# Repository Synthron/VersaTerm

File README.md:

# VersaTerm

Adaptation of https://github.com/dhansel/VersaTerm/tree/main

## Changes

- Integrated Pi Pico and MAX3232
- Additional USB A Port for Power to Display
- Integrated 3V3 SMPS
- No 12V connector, Power Supply via USB or UART (5V TTL only)

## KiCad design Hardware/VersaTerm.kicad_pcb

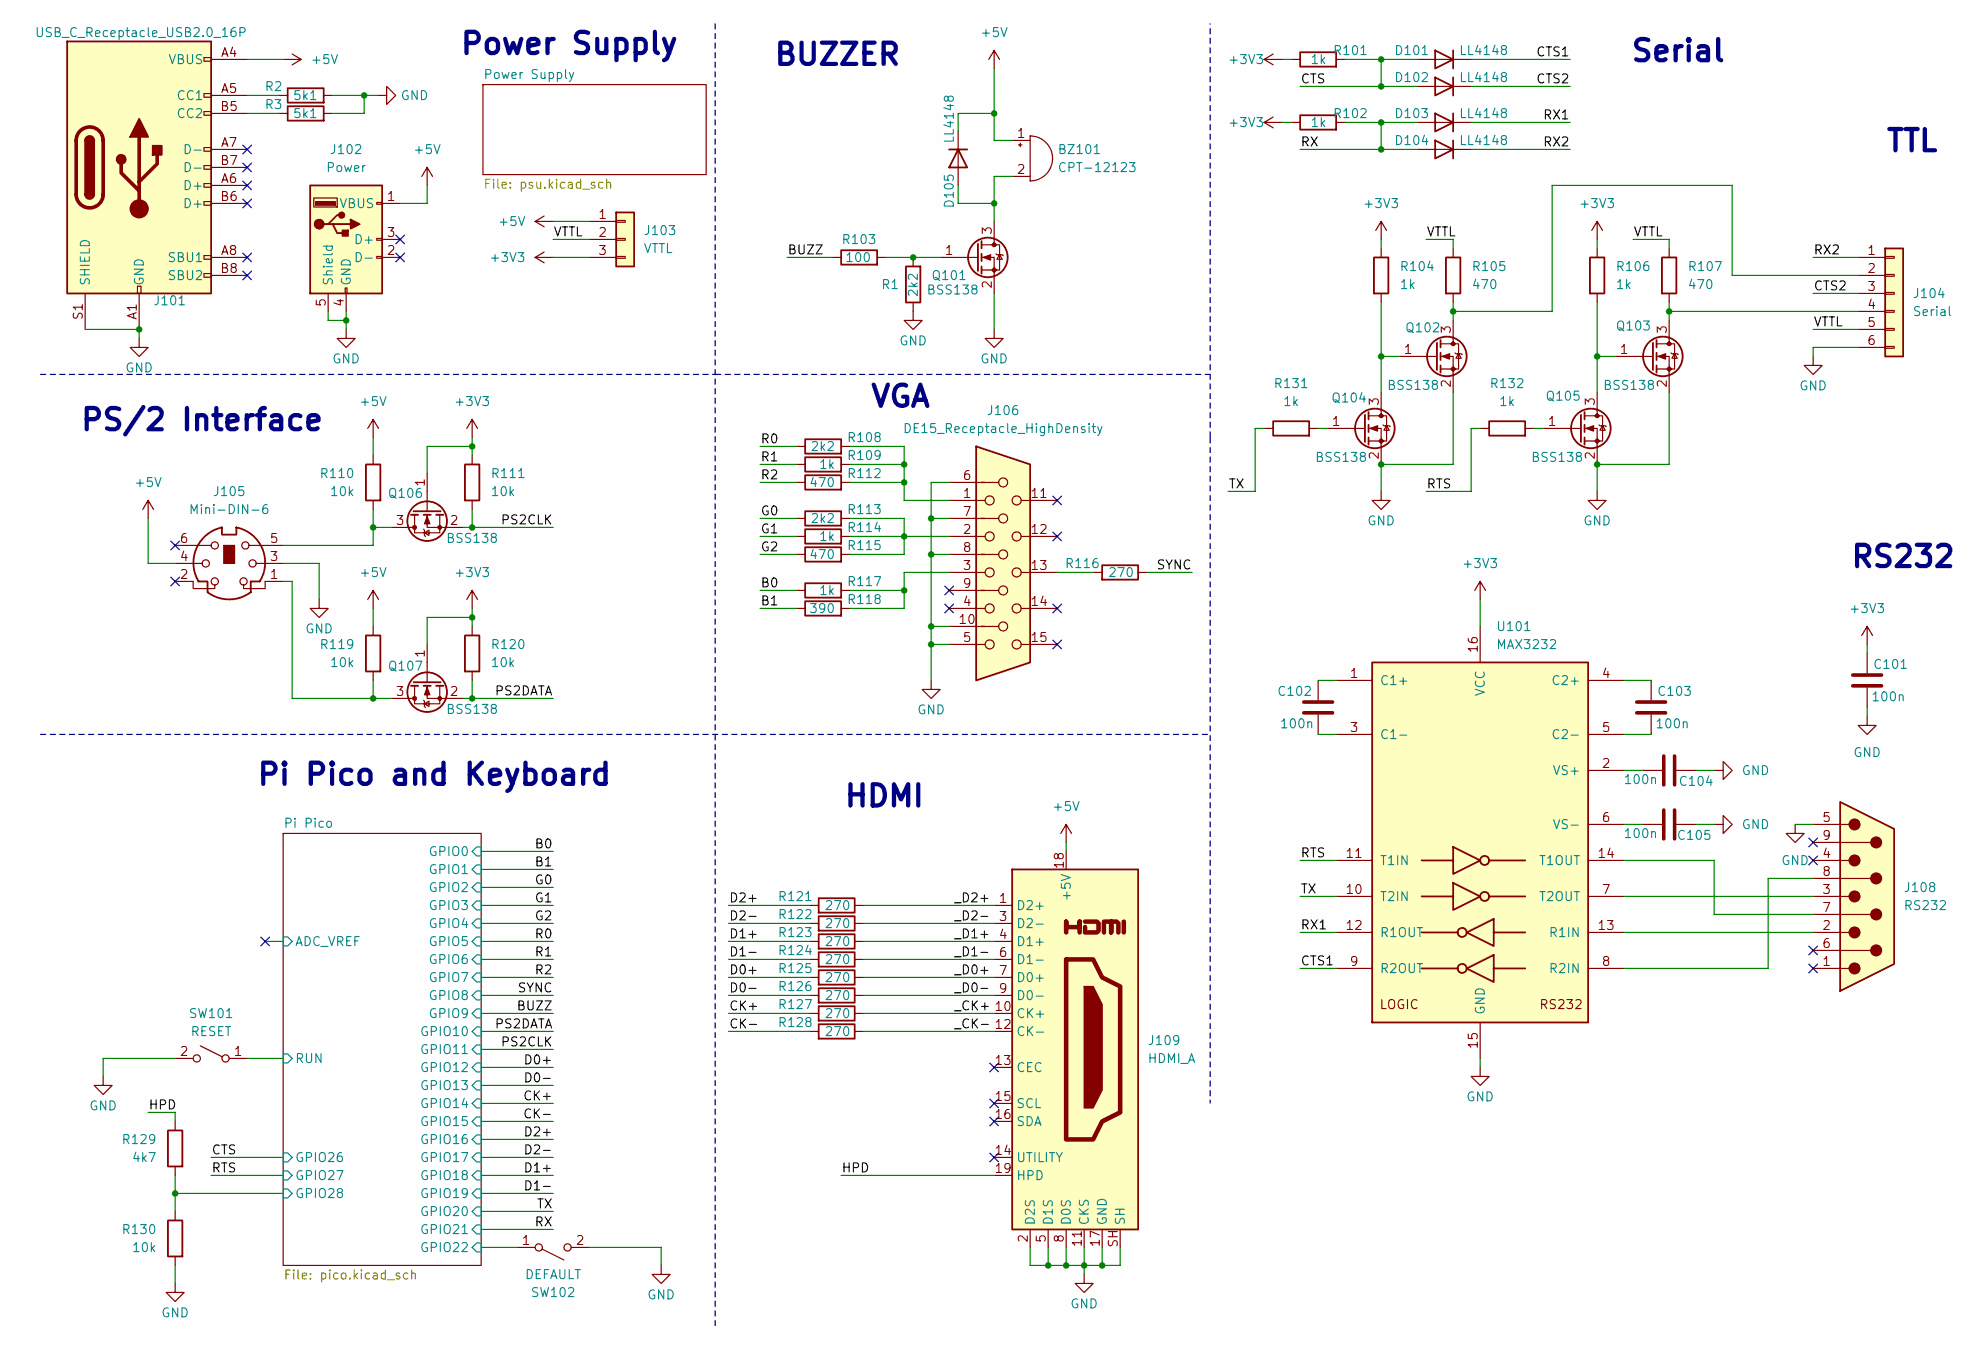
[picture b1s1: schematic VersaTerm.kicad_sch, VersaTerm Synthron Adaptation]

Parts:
BZ101: CPT-12123; Buzzer_Mallory_AST1240MLQ
C101, C102, C103, C104, C105: 100n; C_0805_2012Metric
D101, D102, D103, D104, D105: LL4148; D_MiniMELF
J101: USB_C_Receptacle_USB2.0_16P; USB_C_Receptacle_G-Switch_GT-USB-7010ASV
J102: Power; USB_A_CONNFLY_DS1095-WNR0
J103: VTTL; PinHeader_1x03_P2.54mm_Horizontal
J104: Serial; PinHeader_1x06_P2.54mm_Horizontal
J105: Mini-DIN-6; 57500711
J106: DE15_Receptacle_HighDensity; DSUB-15-HD_Female_Horizontal_P2.29x1.98mm_EdgePinOffset8.35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
J108: RS232; DSUB-9_Male_Horizontal_P2.77x2.84mm_EdgePinOffset7.70mm_Hou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
J109: HDMI_A; AMPHENOL_10029449-111RLF
Q101, Q102, Q103, Q104, Q105, Q106, Q107: BSS138; SOT-23
R1, R108, R113: 2k2; R_0805_2012Metric
R2, R3: 5k1; R_0805_2012Metric
R101, R102, R104, R106, R109, R114, R117, R131, R132: 1k; R_0805_2012Metric
R103: 100; R_0805_2012Metric
R105, R107, R112, R115: 470; R_0805_2012Metric
R110, R111, R119, R120, R130: 10k; R_0805_2012Metric
R116, R121, R122, R123, R124, R125, R126, R127, R128: 270; R_0805_2012Metric
R118: 390; R_0805_2012Metric
R129: 4k7; R_0805_2012Metric
SW101: RESET; SW_SPST_Omron_B3F-315x_Angled
SW102: DEFAULT; SW_SPST_Omron_B3F-315x_Angled
U101: MAX3232; TSSOP-16_4.4x5mm_P0.65mm

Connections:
+3V3: C101.1, J103.3, Q106.1 (G), Q107.1 (G), R101.1, R102.1, R104.1, R106.1, R111.1, R120.1, U101.16 (VCC); also elsewhere on the board
+5V: BZ101.1 (+), D105.1 (K), J101.A4 (VBUS), J101.A9 (VBUS), J101.B4 (VBUS), J101.B9 (VBUS), J102.1 (VBUS), J103.1, J105.4, J109.18 (+5V), R110.1, R119.1; also elsewhere on the board
/B0: R117.1; also elsewhere on the board
/B1: R118.1; also elsewhere on the board
/BUZZ: R103.1; also elsewhere on the board
/CK+: R127.2; also elsewhere on the board
/CK-: R128.2; also elsewhere on the board
/CTS: D101.2 (A), D102.2 (A), R101.2; also elsewhere on the board
/CTS1: D101.1 (K), U101.9 (R2OUT)
/CTS2: D102.1 (K), J104.3
/D0+: R125.2; also elsewhere on the board
/D0-: R126.2; also elsewhere on the board
/D1+: R123.2; also elsewhere on the board
/D1-: R124.2; also elsewhere on the board
/D2+: R121.2; also elsewhere on the board
/D2-: R122.2; also elsewhere on the board
/G0: R113.1; also elsewhere on the board
/G1: R114.1; also elsewhere on the board
/G2: R115.1; also elsewhere on the board
/HPD: J109.19 (HPD), R129.1
/PS2CLK: Q106.2 (S), R111.2; also elsewhere on the board
/PS2DATA: Q107.2 (S), R120.2; also elsewhere on the board
/Pi Pico/ADC2: R129.2, R130.1; also elsewhere on the board
/Pi Pico/GPIO22: SW102.1 (A); also elsewhere on the board
/Pi Pico/RUN: SW101.1 (A); also elsewhere on the board
/R0: R108.1; also elsewhere on the board
/R1: R109.1; also elsewhere on the board
/R2: R112.1; also elsewhere on the board
/RTS: R132.1, U101.11 (T1IN); also elsewhere on the board
/RX: D103.2 (A), D104.2 (A), R102.2; also elsewhere on the board
/RX1: D103.1 (K), U101.12 (R1OUT)
/RX2: D104.1 (K), J104.1
/SYNC: R116.1; also elsewhere on the board
/TX: R131.1, U101.10 (T2IN); also elsewhere on the board
/VTTL: J103.2, J104.5, R105.1, R107.1
/_CK+: J109.10 (CK+), R127.1
/_CK-: J109.12 (CK-), R128.1
/_D0+: J109.7 (D0+), R125.1
/_D0-: J109.9 (D0-), R126.1
/_D1+: J109.4 (D1+), R123.1
/_D1-: J109.6 (D1-), R124.1
/_D2+: J109.1 (D2+), R121.1
/_D2-: J109.3 (D2-), R122.1
GND: C101.2, C104.2, C105.2, J101.A1 (GND), J101.A12 (GND), J101.B1 (GND), J101.B12 (GND), J101.S1 (SHIELD), J102.4 (GND), J102.5 (Shield), J104.6, J105.3, J106.5, J106.6, J106.7, J106.8, J106.10, J108.5, J109.2 (D2S), J109.5 (D1S), J109.8 (D0S), J109.11 (CKS), J109.17 (GND), J109.SH, Q101.2 (S), Q102.2 (S), Q103.2 (S), Q104.2 (S), Q105.2 (S), R1.1, R2.2, R3.2, R130.2, SW101.2 (B), SW102.2 (B), U101.15 (GND); also elsewhere on the board
unnamed: BZ101.2 (-), D105.2 (A), Q101.3 (D)
unnamed: J101.A5 (CC1), R2.1
unnamed: J101.B5 (CC2), R3.1
unnamed: J104.2, Q102.3 (D), R105.2
unnamed: J104.4, Q103.3 (D), R107.2
unnamed: J106.1, R108.2, R109.2, R112.2
unnamed: J106.2, R113.2, R114.2, R115.2
unnamed: J106.3, R117.2, R118.2
unnamed: J106.13, R116.2
unnamed: Q101.1 (G), R1.2, R103.2
unnamed: Q102.1 (G), Q104.3 (D), R104.2
unnamed: Q103.1 (G), Q105.3 (D), R106.2
unnamed: Q104.1 (G), R131.2
unnamed: Q105.1 (G), R132.2
unnamed: J105.5, Q106.3 (D), R110.2
unnamed: J105.1, Q107.3 (D), R119.2
unnamed: C102.1, U101.1 (C1+)
unnamed: C102.2, U101.3 (C1-)
unnamed: C103.1, U101.4 (C2+)
unnamed: C103.2, U101.5 (C2-)
unnamed: J108.2, U101.13 (R1IN)
unnamed: J108.8, U101.8 (R2IN)
unnamed: J108.7, U101.14 (T1OUT)
unnamed: J108.3, U101.7 (T2OUT)
unnamed: C104.1, U101.2 (VS+)
unnamed: C105.1, U101.6 (VS-)

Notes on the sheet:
Pi Pico and Keyboard
Serial
HDMI
BUZZER
VGA
TTL
PS/2 Interface
Power Supply
RS232

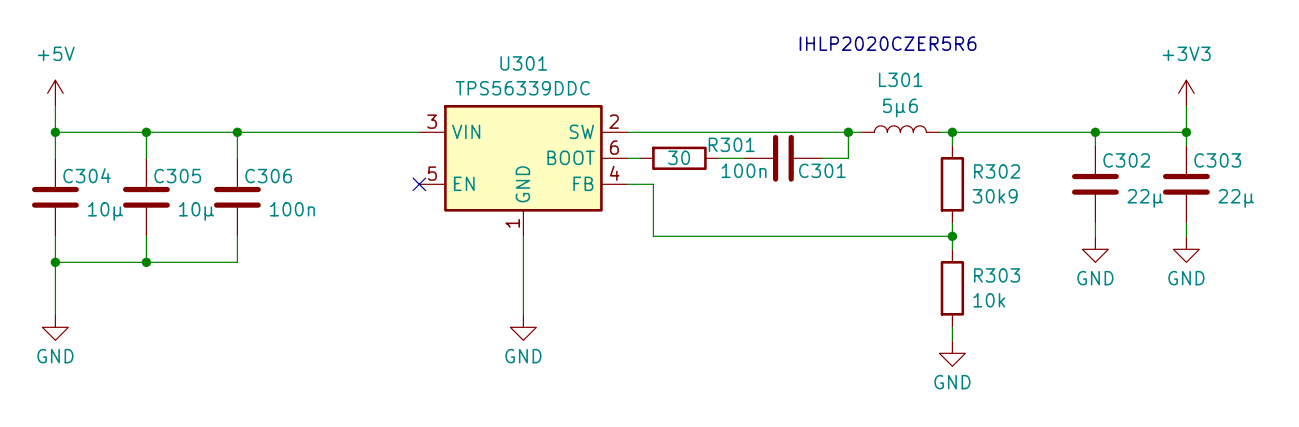
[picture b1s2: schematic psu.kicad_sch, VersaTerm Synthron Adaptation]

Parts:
C301, C306: 100n; C_0805_2012Metric
C302, C303: 22µ; C_0805_2012Metric
C304, C305: 10µ; C_0805_2012Metric
L301: 5µ6; L_Vishay_IHLP-2020
R301: 30; R_0805_2012Metric
R302: 30k9; R_0805_2012Metric
R303: 10k; R_0805_2012Metric
U301: TPS56339DDC; SOT-23-6

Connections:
+3V3: C302.1, C303.1, L301.2, R302.1; also elsewhere on the board
+5V: C304.1, C305.1, C306.1, U301.3 (VIN); also elsewhere on the board
GND: C302.2, C303.2, C304.2, C305.2, C306.2, R303.2, U301.1 (GND); also elsewhere on the board
unnamed: C301.1, R301.1
unnamed: R301.2, U301.6 (BOOT)
unnamed: R302.2, R303.1, U301.4 (FB)
unnamed: C301.2, L301.1, U301.2 (SW)

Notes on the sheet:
IHLP2020CZER5R6

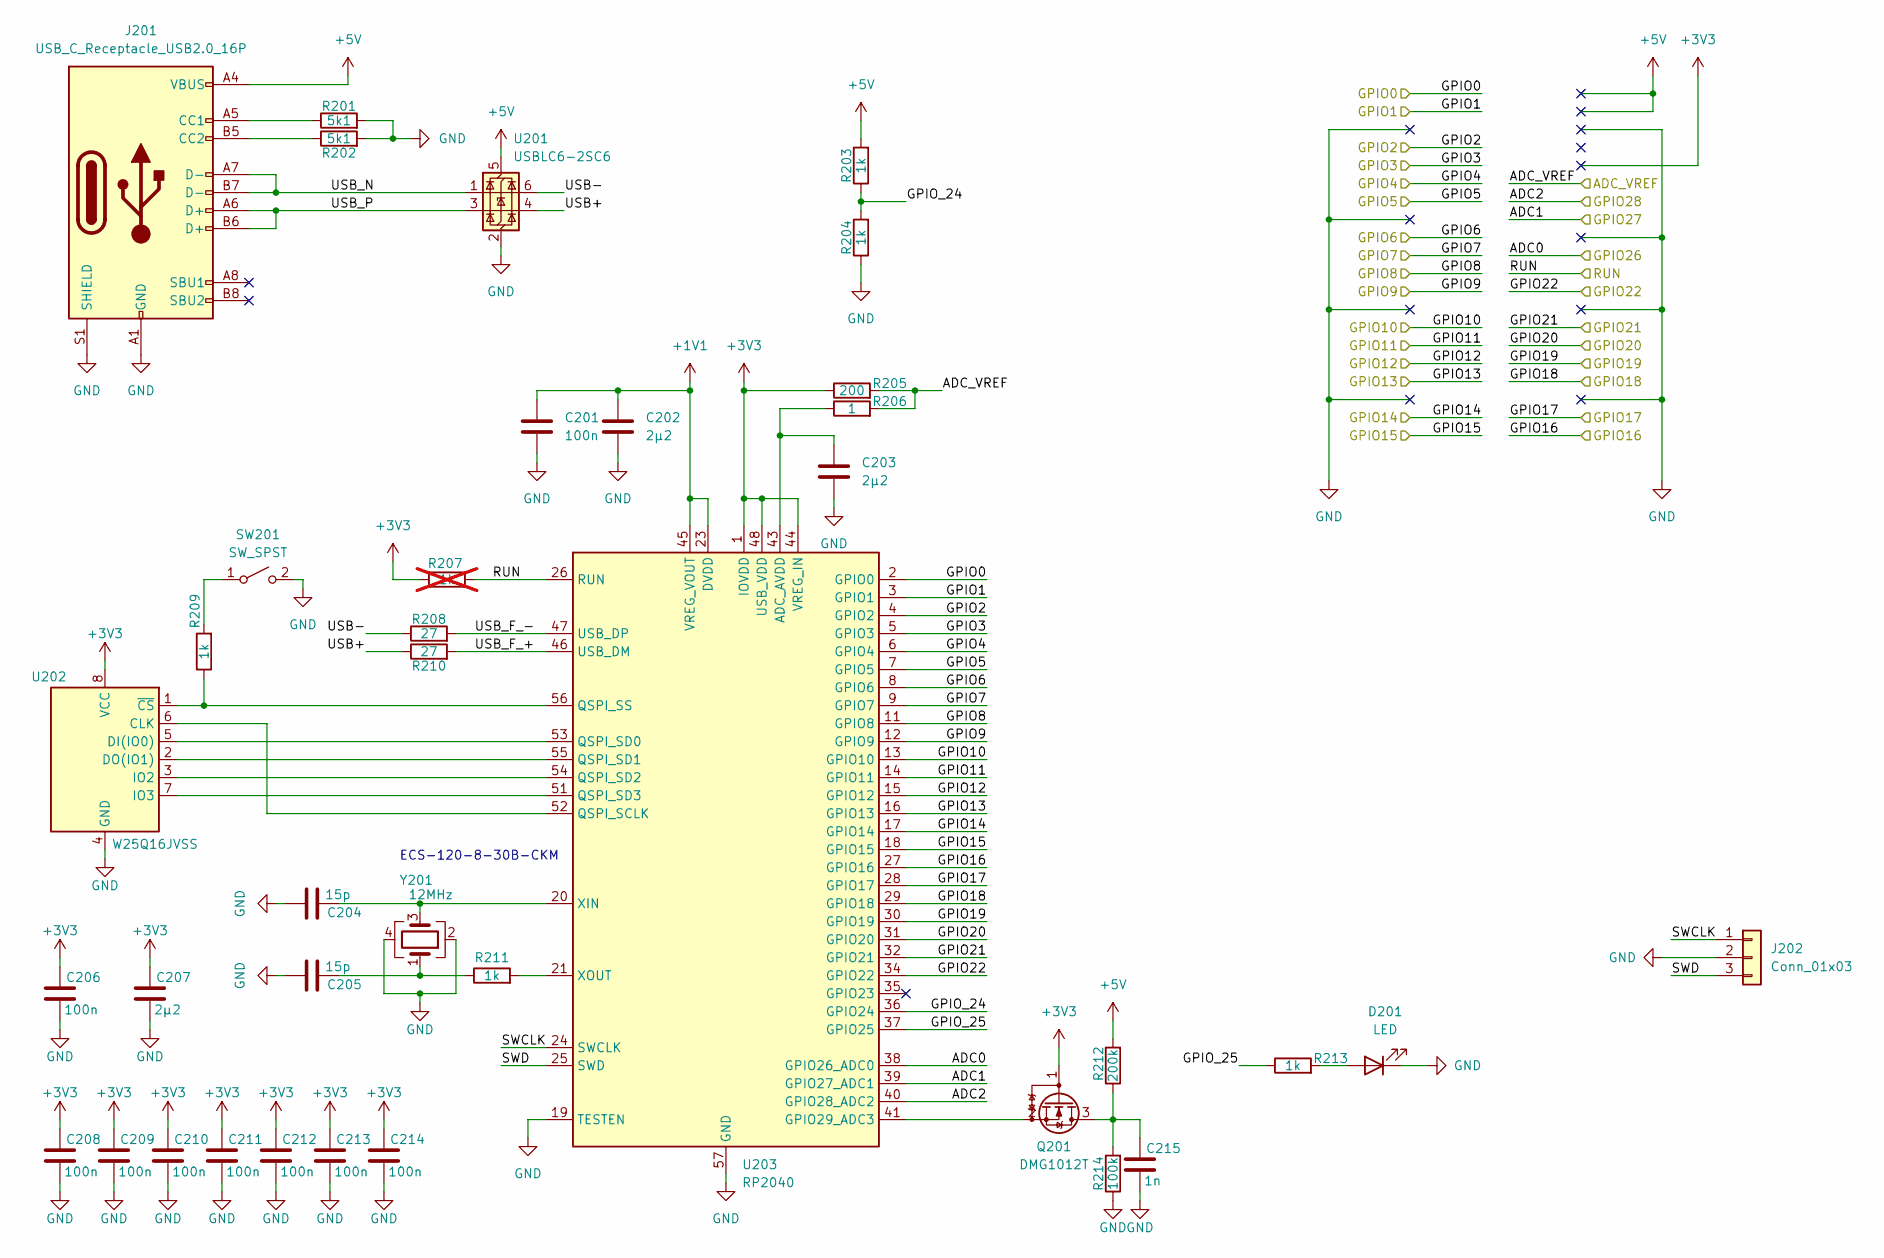
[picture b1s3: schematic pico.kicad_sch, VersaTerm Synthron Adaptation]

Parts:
C201, C206, C208, C209, C210, C211, C212, C213, C214: 100n; C_0805_2012Metric
C202, C203, C207: 2µ2; C_0805_2012Metric
C204, C205: 15p; C_0805_2012Metric
C215: 1n; C_0805_2012Metric
D201: LED; LED_0805_2012Metric
J201: USB_C_Receptacle_USB2.0_16P; USB_C_Receptacle_G-Switch_GT-USB-7010ASV
J202: Conn_01x03; PinHeader_1x03_P2.54mm_Vertical
Q201: DMG1012T; SOT-323_SC-70
R201, R202: 5k1; R_0805_2012Metric
R203, R204, R209, R211, R213: 1k; R_0805_2012Metric
R205: 200; R_0805_2012Metric
R206: 1; R_0805_2012Metric
R207: 1k; R_0805_2012Metric; not fitted
R208, R210: 27; R_0805_2012Metric
R212: 200k; R_0805_2012Metric
R214: 100k; R_0805_2012Metric
SW201: SW_SPST; SW_SPST_Omron_B3F-315x_Angled
U201: USBLC6-2SC6; SOT-23-6
U202: W25Q16JVSS; SOIC-8_5.23x5.23mm_P1.27mm
U203: RP2040; QFN-56-1EP_7x7mm_P0.4mm_EP3.2x3.2mm_ThermalVias
Y201: 12MHz; Crystal_SMD_3225-4Pin_3.2x2.5mm

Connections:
+1V1: C201.1, C202.1, U203.23 (DVDD), U203.45 (VREG_VOUT), U203.50 (DVDD)
+3V3: C206.1, C207.1, C208.1, C209.1, C210.1, C211.1, C212.1, C213.1, C214.1, Q201.1 (G), R205.1, R207.2, U202.8 (VCC), U203.1 (IOVDD), U203.10 (IOVDD), U203.22 (IOVDD), U203.33 (IOVDD), U203.42 (IOVDD), U203.44 (VREG_IN), U203.48 (USB_VDD), U203.49 (IOVDD); also elsewhere on the board
+5V: J201.A4 (VBUS), J201.A9 (VBUS), J201.B4 (VBUS), J201.B9 (VBUS), R203.2, R212.2, U201.5 (VBUS); also elsewhere on the board
/B0: U203.2 (GPIO0); also elsewhere on the board
/B1: U203.3 (GPIO1); also elsewhere on the board
/BUZZ: U203.12 (GPIO9); also elsewhere on the board
/CK+: U203.17 (GPIO14); also elsewhere on the board
/CK-: U203.18 (GPIO15); also elsewhere on the board
/CTS: U203.38 (GPIO26_ADC0); also elsewhere on the board
/D0+: U203.15 (GPIO12); also elsewhere on the board
/D0-: U203.16 (GPIO13); also elsewhere on the board
/D1+: U203.29 (GPIO18); also elsewhere on the board
/D1-: U203.30 (GPIO19); also elsewhere on the board
/D2+: U203.27 (GPIO16); also elsewhere on the board
/D2-: U203.28 (GPIO17); also elsewhere on the board
/G0: U203.4 (GPIO2); also elsewhere on the board
/G1: U203.5 (GPIO3); also elsewhere on the board
/G2: U203.6 (GPIO4); also elsewhere on the board
/K1+: R210.1, U201.4 (I/O2)
/K1-: R208.1, U201.6 (I/O1)
/PS2CLK: U203.14 (GPIO11); also elsewhere on the board
/PS2DATA: U203.13 (GPIO10); also elsewhere on the board
/Pi Pico/ADC2: U203.40 (GPIO28_ADC2); also elsewhere on the board
/Pi Pico/ADC_VREF: R205.2, R206.2
/Pi Pico/GPIO22: U203.34 (GPIO22); also elsewhere on the board
/Pi Pico/GPIO_24: R203.1, R204.2, U203.36 (GPIO24)
/Pi Pico/GPIO_25: R213.1, U203.37 (GPIO25)
/Pi Pico/RUN: R207.1, U203.26 (RUN); also elsewhere on the board
/Pi Pico/SWCLK: J202.1, U203.24 (SWCLK)
/Pi Pico/SWD: J202.3, U203.25 (SWD)
/Pi Pico/USB_F_+: R210.2, U203.46 (USB_DM)
/Pi Pico/USB_F_-: R208.2, U203.47 (USB_DP)
/Pi Pico/USB_N: J201.A7 (D-), J201.B7 (D-), U201.1 (I/O1)
/Pi Pico/USB_P: J201.A6 (D+), J201.B6 (D+), U201.3 (I/O2)
/R0: U203.7 (GPIO5); also elsewhere on the board
/R1: U203.8 (GPIO6); also elsewhere on the board
/R2: U203.9 (GPIO7); also elsewhere on the board
/RTS: U203.39 (GPIO27_ADC1); also elsewhere on the board
/RX: U203.32 (GPIO21); also elsewhere on the board
/SYNC: U203.11 (GPIO8); also elsewhere on the board
/TX: U203.31 (GPIO20); also elsewhere on the board
GND: C201.2, C202.2, C203.2, C204.2, C205.2, C206.2, C207.2, C208.2, C209.2, C210.2, C211.2, C212.2, C213.2, C214.2, C215.2, D201.1 (K), J201.A1 (GND), J201.A12 (GND), J201.B1 (GND), J201.B12 (GND), J201.S1 (SHIELD), J202.2, R201.2, R202.2, R204.1, R214.1, SW201.2 (B), U201.2 (GND), U202.4 (GND), U203.19 (TESTEN), U203.57 (GND), Y201.2, Y201.4; also elsewhere on the board
unnamed: C205.1, R211.1, Y201.1
unnamed: D201.2 (A), R213.2
unnamed: J201.A5 (CC1), R201.1
unnamed: J201.B5 (CC2), R202.1
unnamed: C215.1, Q201.3 (D), R212.1, R214.2
unnamed: Q201.2 (S), U203.41 (GPIO29_ADC3)
unnamed: R209.2, SW201.1 (A)
unnamed: U202.6 (CLK), U203.52 (QSPI_SCLK)
unnamed: U202.5 (DI(IO0)), U203.53 (QSPI_SD0)
unnamed: U202.2 (DO(IO1)), U203.55 (QSPI_SD1)
unnamed: U202.3 (IO2), U203.54 (QSPI_SD2)
unnamed: U202.7 (IO3), U203.51 (QSPI_SD3)
unnamed: R209.1, U202.1 (~CS), U203.56 (QSPI_SS)
unnamed: C203.1, R206.1, U203.43 (ADC_AVDD)
unnamed: C204.1, U203.20 (XIN), Y201.3
unnamed: R211.2, U203.21 (XOUT)

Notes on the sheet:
ECS-120-8-30B-CKM

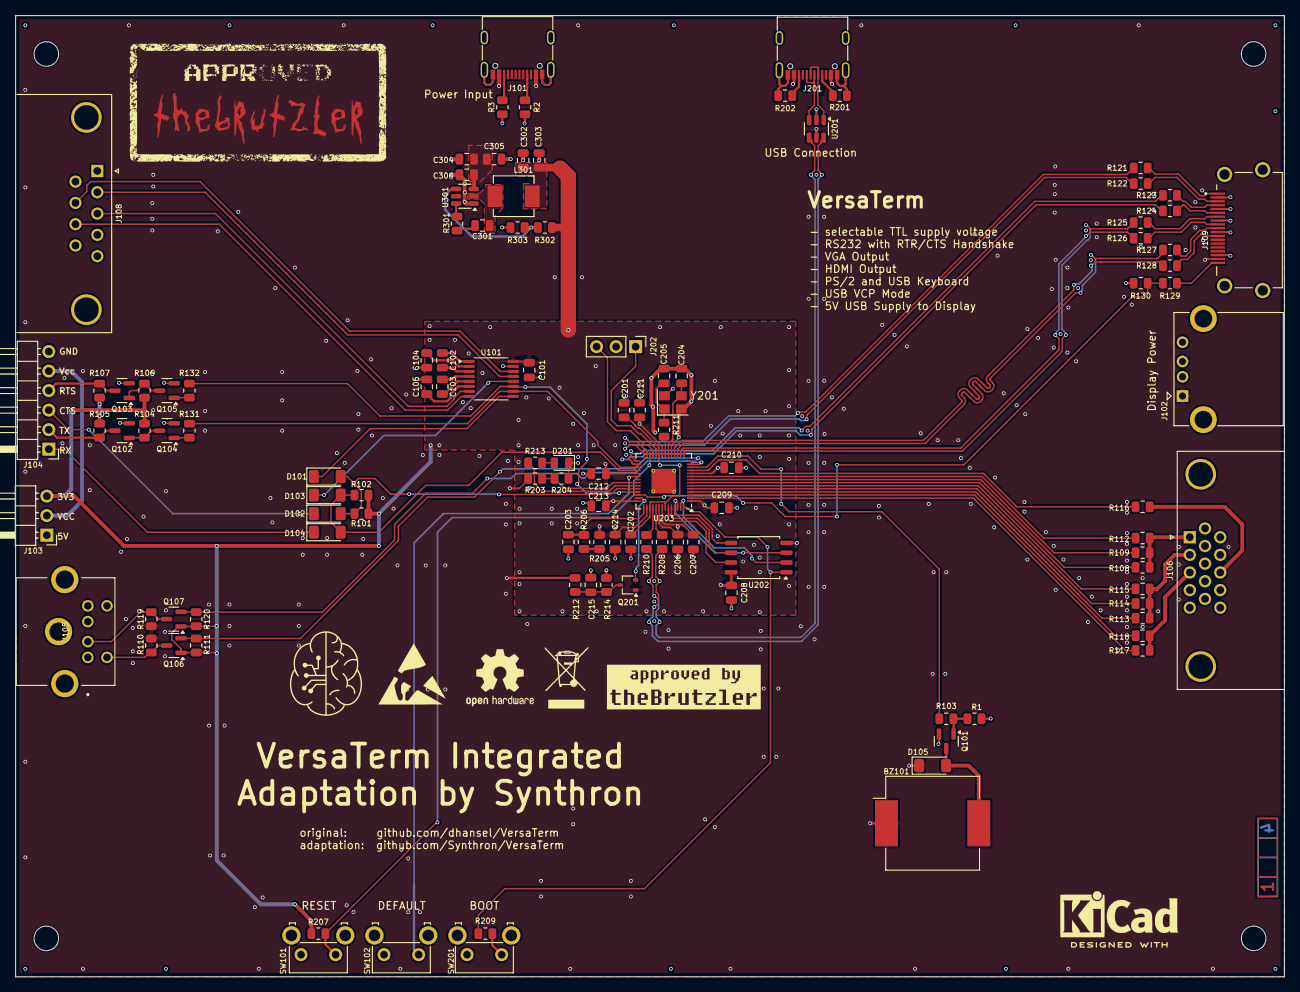
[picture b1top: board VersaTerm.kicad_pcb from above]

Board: 4 copper layers, 165.0 x 125.0 mm, 114 parts (0 on the bottom side), 102 nets.

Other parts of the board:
Ref**: Val**; ladder_4

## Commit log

2024-09-26 Schematic Done
2024-09-29 finalized PCB
2024-10-03 pcb update
2024-10-03 updated version not final reviewed
2024-10-10 rework
2024-10-10 Final Review Version (Update USB Routing)
